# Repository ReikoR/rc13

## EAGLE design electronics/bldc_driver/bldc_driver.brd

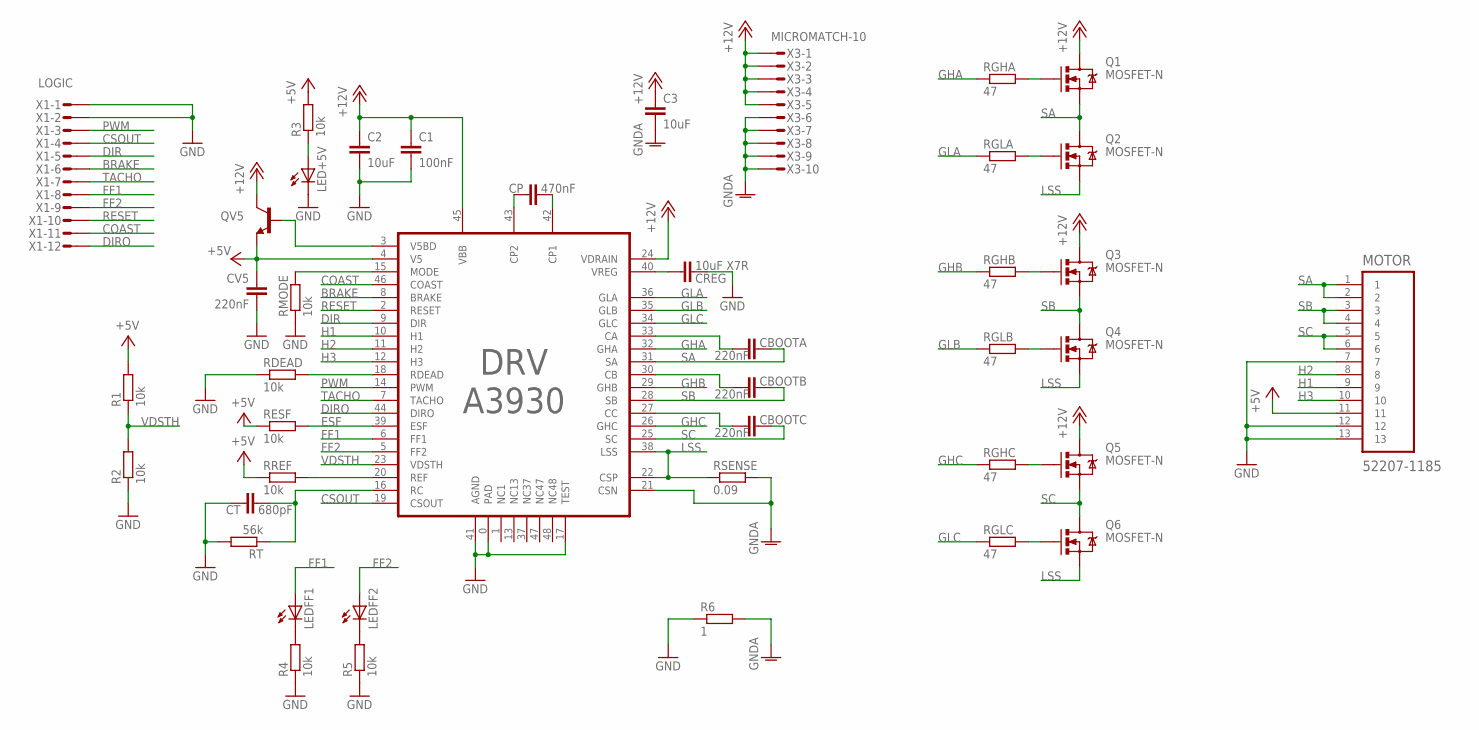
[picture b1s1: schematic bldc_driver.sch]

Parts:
C1: 100nF; C0603
C2, C3: 10uF; C1206K
CBOOTA: 220nF; C0603
CBOOTB: 220nF; C0603
CBOOTC: 220nF; C0603
CP: 470nF; C0603
CREG: 10uF X7R; C1206K
CT: 680pF; C0603
CV5: 220nF; C0603
DRV: A3930; LQFP-48
LED+5V: LEDCHIPLED_0603; CHIPLED_0603
LEDFF1, LEDFF2: LEDCHIPLED_0603; CHIPLED_0603
MOTOR: 52207-1185; MOLEX_52207-1185
Q1, Q2, Q3, Q4, Q5, Q6: MOSFET-N; SO08
QV5: TRANSISTOR_NPNSOT23; SOT23
R1, R2, R3, R4, R5: 10k; R0603
R6: 1; R0603
RDEAD: 10k; R0603
RESF: 10k; R0603
RGHA: 47; R0603
RGHB: 47; R0603
RGHC: 47; R0603
RGLA: 47; R0603
RGLB: 47; R0603
RGLC: 47; R0603
RMODE: 10k; R0603
RREF: 10k; R0603
RSENSE: 0.09; R2010
RT: 56k; R0603
X1: LOGIC; MICROMATCH-12
X3: MICROMATCH-10

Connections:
+5V: CV5.2, DRV.4 (V5), MOTOR.11, QV5.2 (E), R1.2, R3.2, RESF.1, RREF.1
+12V: C1.1, C2.1, C3.1, DRV.24 (VDRAIN), DRV.45 (VBB), Q1.5 (D), Q1.6 (D), Q1.7 (D), Q1.8 (D), Q3.5 (D), Q3.6 (D), Q3.7 (D), Q3.8 (D), Q5.5 (D), Q5.6 (D), Q5.7 (D), Q5.8 (D), QV5.3 (C), X3.1, X3.2, X3.3, X3.4, X3.5
BRAKE: DRV.8 (BRAKE), X1.6
COAST: DRV.46 (COAST), X1.11
CSOUT: DRV.19 (CSOUT), X1.4
DIR: DRV.9 (DIR), X1.5
DIRO: DRV.44 (DIRO), X1.12
ESF: DRV.39 (ESF), RESF.2
FF1: DRV.6 (FF1), LEDFF1.A, X1.8
FF2: DRV.5 (FF2), LEDFF2.A, X1.9
GHA: DRV.32 (GHA), RGHA.1
GHB: DRV.29 (GHB), RGHB.1
GHC: DRV.26 (GHC), RGHC.1
GLA: DRV.36 (GLA), RGLA.1
GLB: DRV.35 (GLB), RGLB.1
GLC: DRV.34 (GLC), RGLC.1
GND: C1.2, C2.2, CREG.2, CT.2, CV5.1, DRV.0 (PAD), DRV.17 (TEST), DRV.41 (AGND), LED+5V.C, MOTOR.7, MOTOR.12, MOTOR.13, R2.1, R4.1, R5.1, R6.1, RDEAD.1, RMODE.1, RT.2, X1.1, X1.2
GNDA: C3.2, DRV.21 (CSN), R6.2, RSENSE.2, X3.6, X3.7, X3.8, X3.9, X3.10
H1: DRV.10 (H1), MOTOR.9
H2: DRV.11 (H2), MOTOR.8
H3: DRV.12 (H3), MOTOR.10
LSS: DRV.22 (CSP), DRV.38 (LSS), Q2.1 (S), Q2.2 (S), Q2.3 (S), Q4.1 (S), Q4.2 (S), Q4.3 (S), Q6.1 (S), Q6.2 (S), Q6.3 (S), RSENSE.1
unnamed: Q1.4 (G), RGHA.2
unnamed: Q2.4 (G), RGLA.2
unnamed: Q3.4 (G), RGHB.2
unnamed: Q4.4 (G), RGLB.2
unnamed: Q5.4 (G), RGHC.2
unnamed: Q6.4 (G), RGLC.2
unnamed: CBOOTA.1, DRV.33 (CA)
unnamed: CREG.1, DRV.40 (VREG)
unnamed: CT.1, DRV.16 (RC), RT.1
unnamed: CP.1, DRV.42 (CP1)
unnamed: CP.2, DRV.43 (CP2)
unnamed: CBOOTB.1, DRV.30 (CB)
unnamed: DRV.18 (RDEAD), RDEAD.2
unnamed: CBOOTC.1, DRV.27 (CC)
unnamed: LED+5V.A, R3.1
unnamed: DRV.20 (REF), RREF.2
unnamed: DRV.15 (MODE), RMODE.2
unnamed: LEDFF1.C, R4.2
unnamed: LEDFF2.C, R5.2
unnamed: DRV.3 (V5BD), QV5.1 (B)
PWM: DRV.14 (PWM), X1.3
RESET: DRV.2 (RESET), X1.10
SA: CBOOTA.2, DRV.31 (SA), MOTOR.1, MOTOR.2, Q1.1 (S), Q1.2 (S), Q1.3 (S), Q2.5 (D), Q2.6 (D), Q2.7 (D), Q2.8 (D)
SB: CBOOTB.2, DRV.28 (SB), MOTOR.3, MOTOR.4, Q3.1 (S), Q3.2 (S), Q3.3 (S), Q4.5 (D), Q4.6 (D), Q4.7 (D), Q4.8 (D)
SC: CBOOTC.2, DRV.25 (SC), MOTOR.5, MOTOR.6, Q5.1 (S), Q5.2 (S), Q5.3 (S), Q6.5 (D), Q6.6 (D), Q6.7 (D), Q6.8 (D)
TACHO: DRV.7 (TACHO), X1.7
VDSTH: DRV.23 (VDSTH), R1.1, R2.2

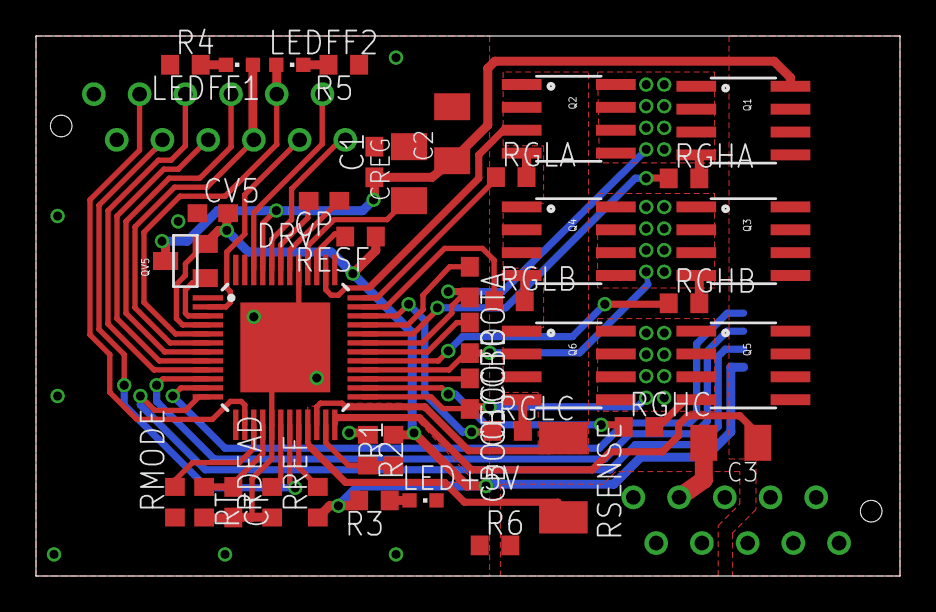
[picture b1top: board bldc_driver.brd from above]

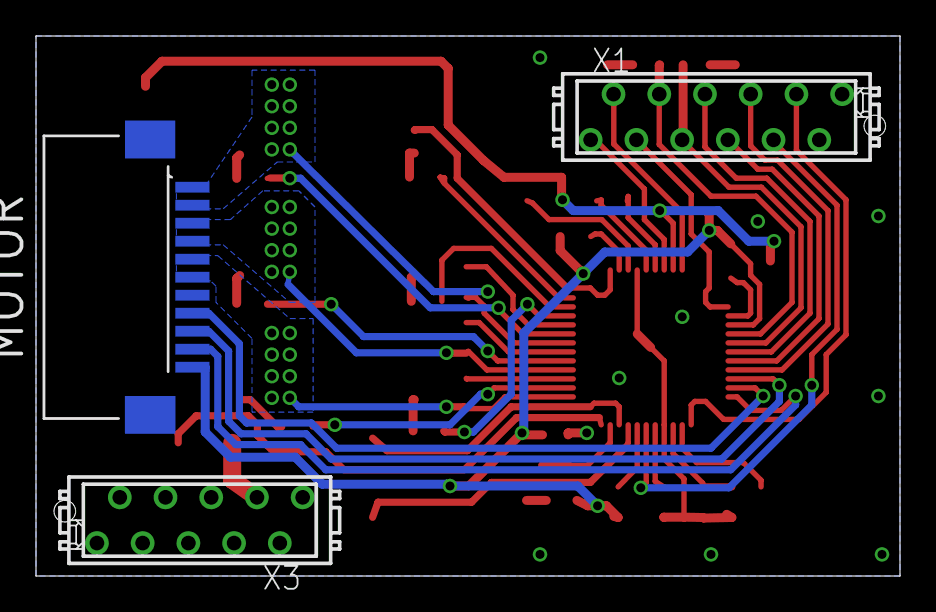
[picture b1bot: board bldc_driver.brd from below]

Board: 2 copper layers, 48.0 x 30.0 mm, 42 parts (3 on the bottom side), 49 nets.

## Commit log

2013-02-28 Added mechanical parts based on Skuba's drawings
2013-02-28 Updated internal gears
2013-03-09 Created a3930 and motor connector Eagle parts, created initial BLDC driver schematic
2013-03-09 Created LiPo and coilgun capacitor placeholders
2013-03-10 Removed 5V pass through transistor
2013-03-10 Removed Eagle backup files
2013-03-14 Started routing motor driver board
2013-03-14 Routed motor driver board
2013-03-21 Adjusted some mechanical parts and added initial electronic and electrical parts
2013-03-25 Updated Eagle library: included proper A3930, motor connector and resonator parts
2013-03-25 Lisan omaltpoolt muudetud failid
2013-03-26 Did some motor driver board routing
2013-03-26 väiksed kohendused
2013-03-26 väiksed kohandused
2013-03-30 Added pass through transistor for +5V, added +5V and fault LEDs, separated driver and noisy ground with 1 ohm resistor, added 2 GNDs to logic connector, added holes for micro-match connectors
2013-04-01 Changed motor driver board logic connector position a bit
2013-04-02 Small motor driver board changes
2013-04-06 Põhiplaat
2013-04-06 Põhi
2013-04-06 Eemaldasin uue kataloogi ja lisan lihtsalt electronic'si alla
2013-04-06 Põhiplaat(finally....)
2013-04-09 Põhiplaat(ROM-addon)
2013-04-11 Updated some wheel parts
2013-04-17 Added internal gear drawing
2013-04-17 Plaadi update
2013-04-20 Added internal gear drawing pdf
2013-04-22 Muudatused
2013-04-23 Põhiplaat(final 1)
2013-04-26 Pisimuudatused
2013-05-11 joonised Maunole
2013-05-13 Changed drive units to accommodate 70 teeth internal gears, changed bottom plate to make enough room for encoders
2013-05-13 koostejoonis
2013-05-13 pisiparandus
2013-05-13 pisilisa
2013-05-21 Added motor shaft extensions, corrected encoder mount hole positions in bottom plate
2013-05-30 Prepared bldc driver for order
2013-06-16 Plaadi uuendus
2013-08-28 Ver 2.0 Lisatud LEDid ja natuke putitatud.
2013-12-05 Põhiplaat V3 Lisatud USB läbi FTDI kivi, UART suhtlus. Parandatud vead FPGA programmeeritavaks muutmisel. Parandatud Flash mälu daisy-chain.

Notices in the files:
parts and their libraries:
SparkFun-DiscreteSemi: Licensing: CC v3.0 Share-Alike You are welcome to use this library for commercial purposes.
